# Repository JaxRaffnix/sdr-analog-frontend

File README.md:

# SDR Analog Frontend

The PCB is ordered from [Aisler](https://aisler.net/p/YPFMCLNO).

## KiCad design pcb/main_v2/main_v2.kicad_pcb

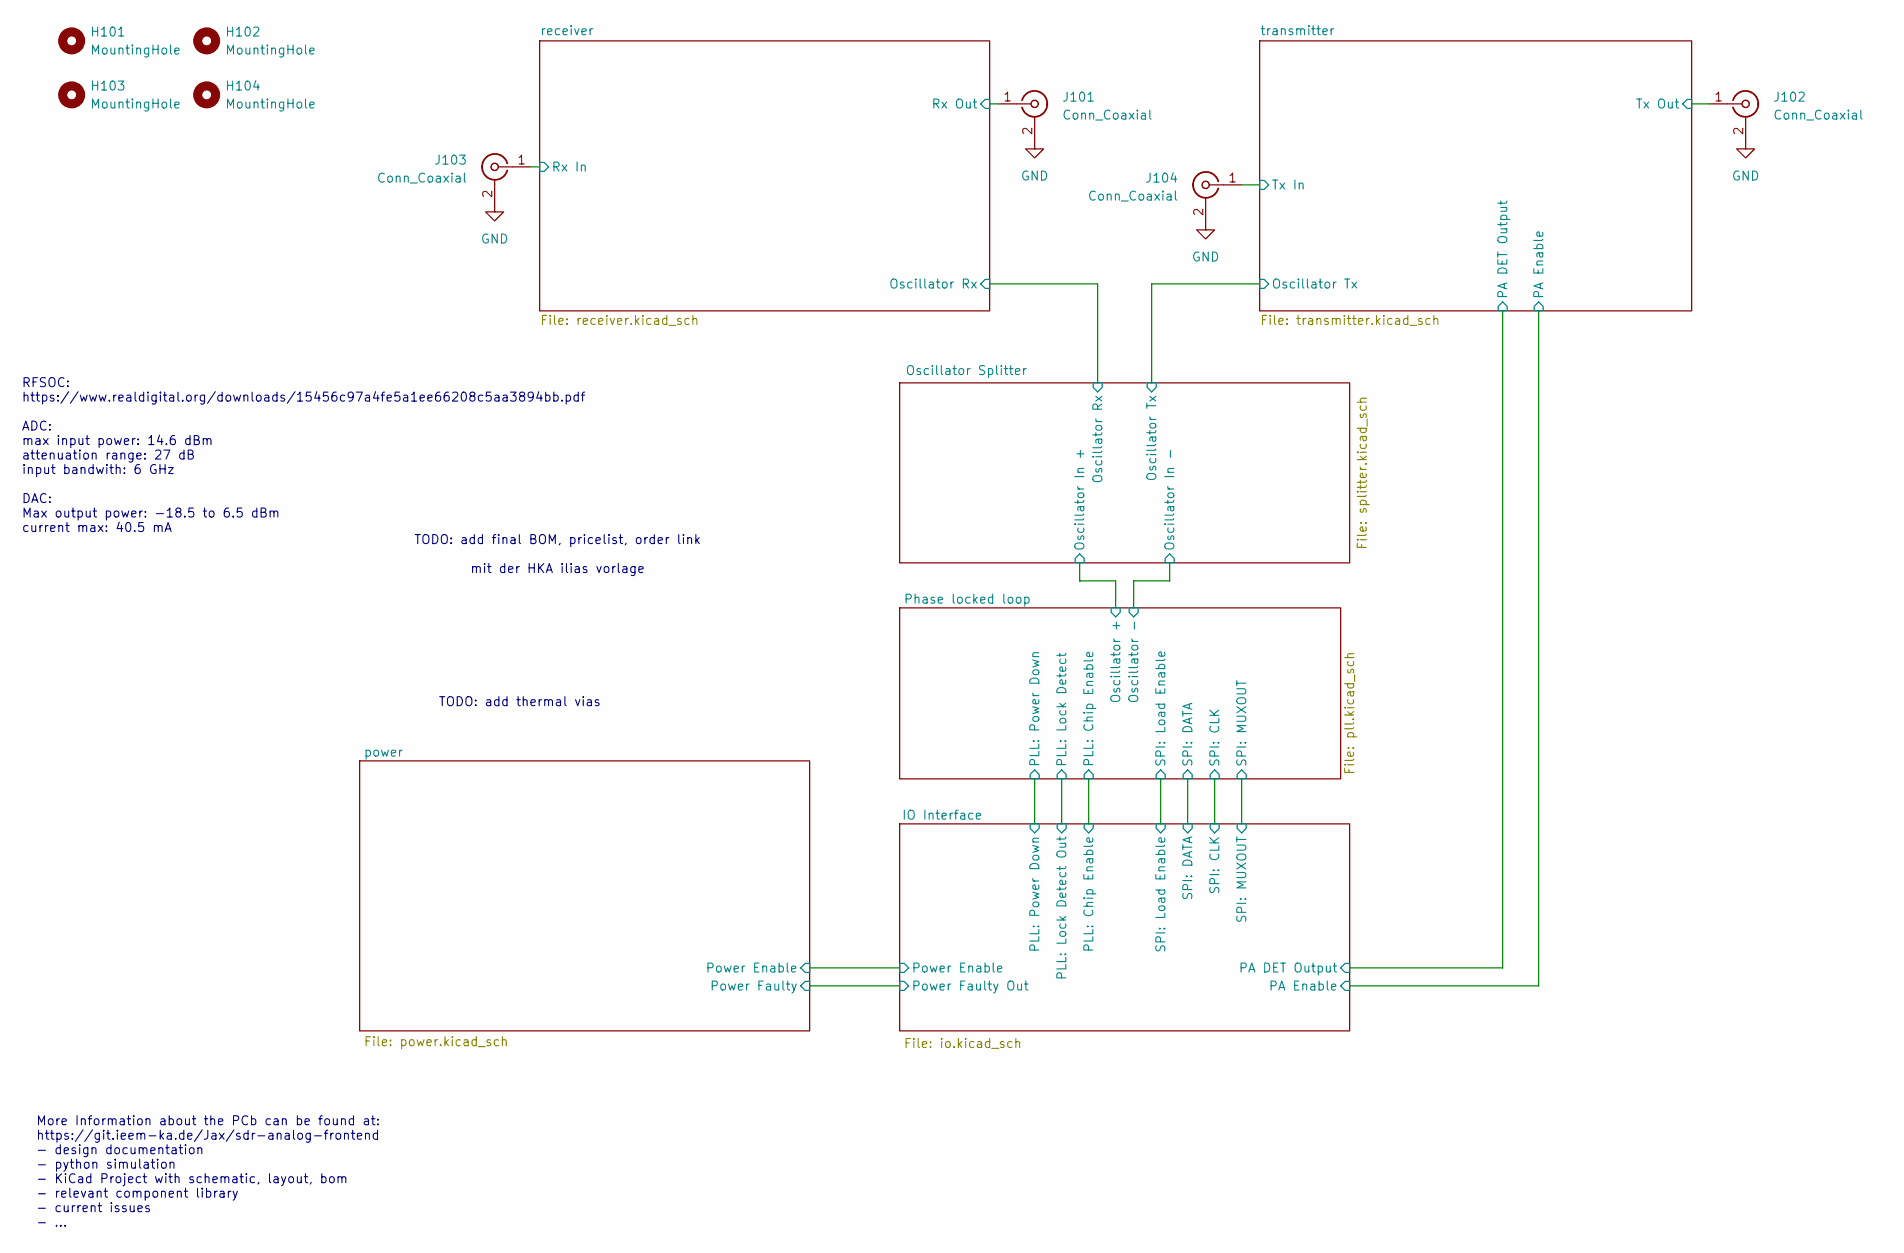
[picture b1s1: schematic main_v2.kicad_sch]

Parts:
H101, H102, H103, H104: MountingHole; MountingHole_2.2mm_M2
J101, J102, J103, J104: Conn_Coaxial; SMA_Amphenol_132289_EdgeMount

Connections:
/receiver/Rx In: J103.1 (In); also elsewhere on the board
/receiver/Rx Out: J101.1 (In); also elsewhere on the board
/transmitter/Tx In: J104.1 (In); also elsewhere on the board
/transmitter/Tx Out: J102.1 (In); also elsewhere on the board
GND: J101.2 (Ext), J102.2 (Ext), J103.2 (Ext), J104.2 (Ext); also elsewhere on the board

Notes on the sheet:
TODO: add final BOM, pricelist, order link mit der HKA ilias vorlage
TODO: add thermal vias
More Information about the PCb can be found at: https://git.ieem-ka.de/Jax/sdr-analog-frontend - design documentation - python simulation - KiCad Project with schematic, layout, bom - relevant component library - current issues - ...
RFSOC: https://www.realdigital.org/downloads/15456c97a4fe5a1ee66208c5aa3894bb.pdf ADC: max input power: 14.6 dBm attenuation range: 27 dB input bandwith: 6 GHz DAC: Max output power: -18.5 to 6.5 dBm current max: 40.5 mA

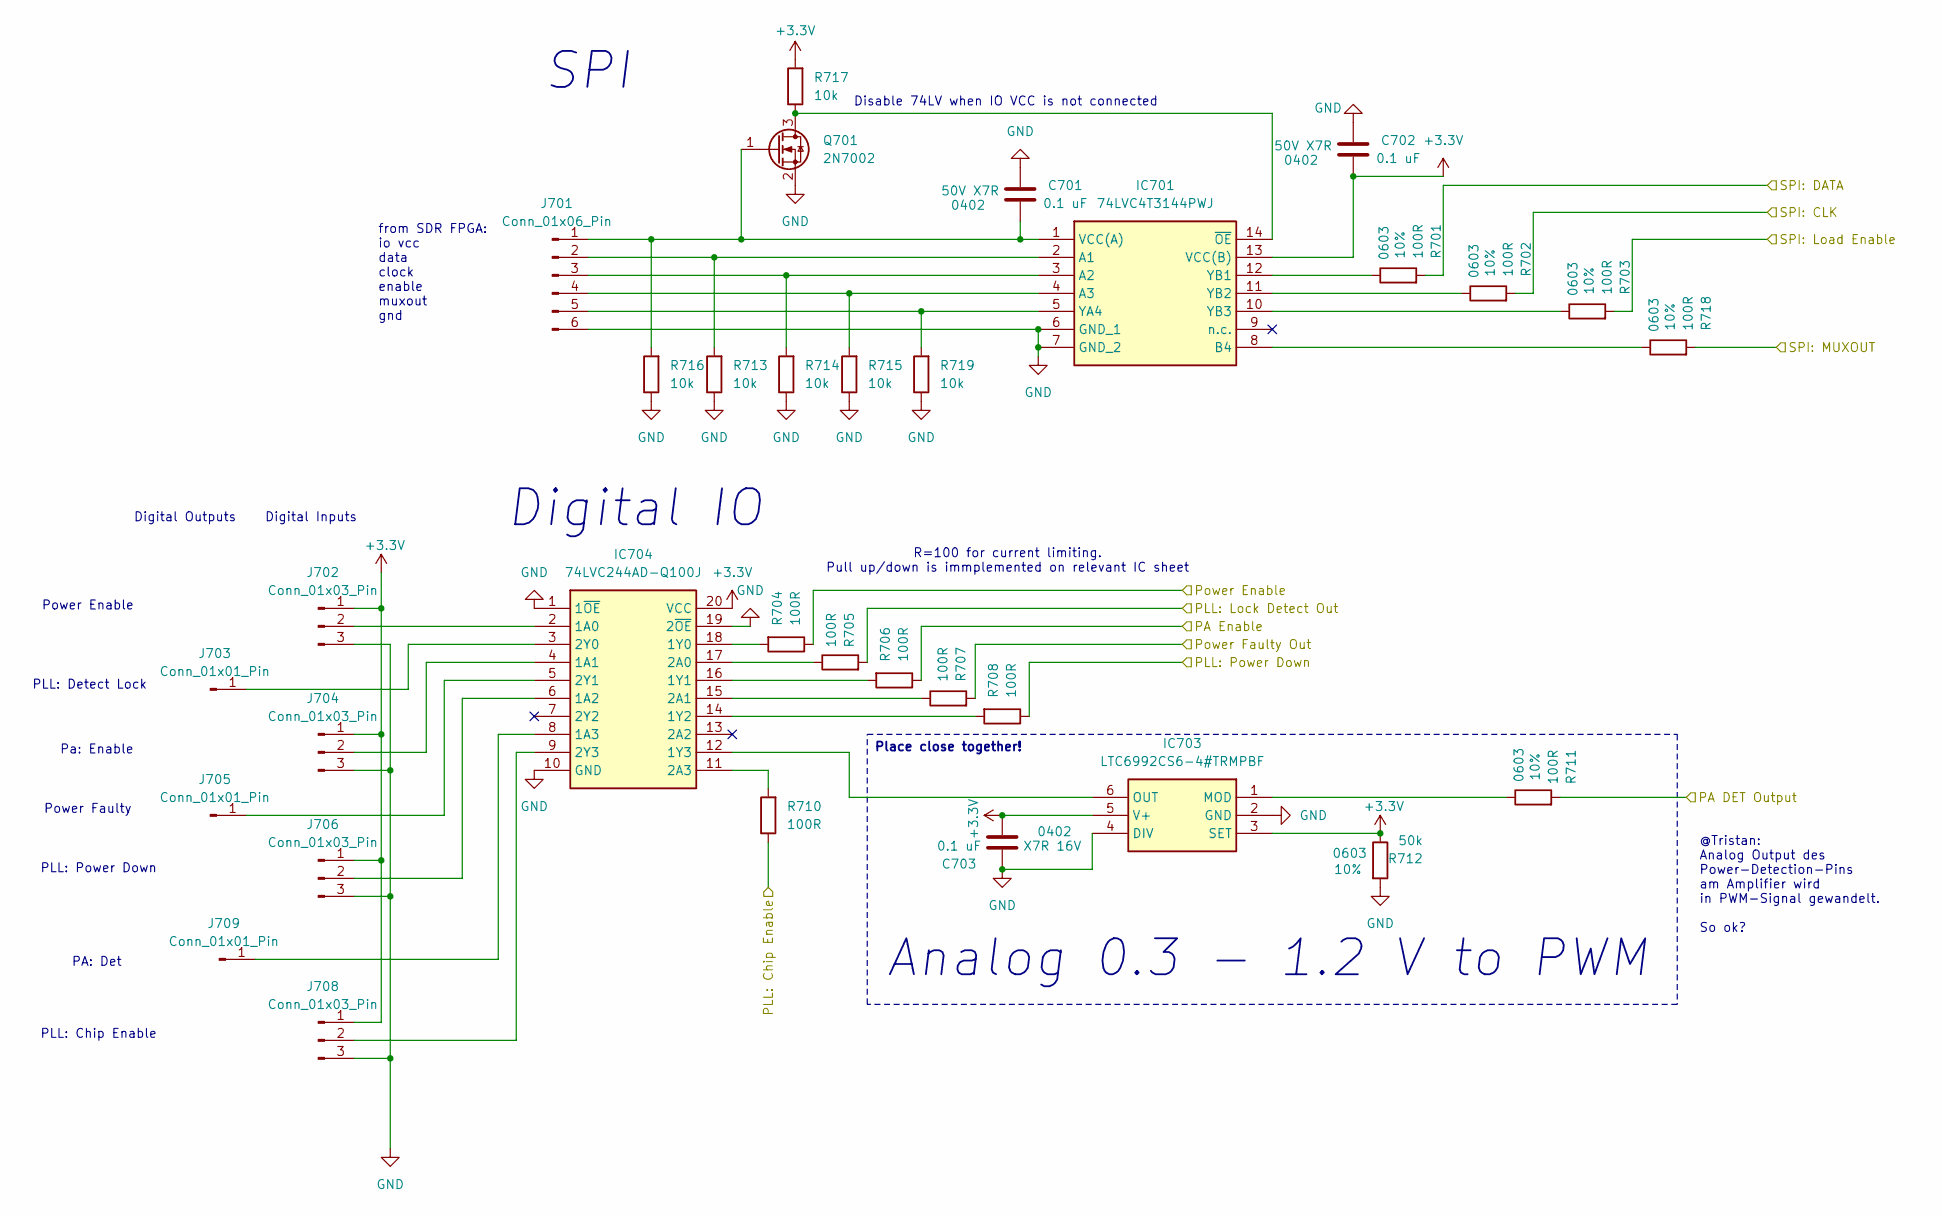
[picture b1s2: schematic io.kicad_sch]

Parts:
C701, C702: 0.1 uF; C_0402_1005Metric; Tolerance ±10%; Voltage 50V
C703: 0.1 uF; C_0402_1005Metric; Tolerance ±10%; Voltage 16V
IC701: 74LVC4T3144PWJ; SOP65P640X110-14N; Mouser Part Number 771-74LVC4T3144PWJ
IC703: LTC6992CS6-4#TRMPBF; SOT95P280X100-6N; Mouser Part Number 584-C6992CS6-4TRMPBF
IC704: 74LVC244AD-Q100J; SOIC127P1032X265-20N; Mouser Part Number 771-74LVC244AD-Q100J
J701: Conn_01x06_Pin; PinHeader_1x06_P2.54mm_Vertical
J702, J704, J706, J708: Conn_01x03_Pin; PinHeader_1x03_P2.54mm_Vertical
J703, J705, J709: Conn_01x01_Pin; PinHeader_1x01_P2.54mm_Vertical
Q701: 2N7002; SOT-23
R701, R702, R703, R711, R718: 100R; R_0603_1608Metric; Tolerance 10%
R704, R705, R706, R707, R708, R710: 100R; R_0603_1608Metric
R712: 50k; R_0603_1608Metric; Tolerance 10%
R713, R714, R715, R716, R717, R719: 10k; R_0603_1608Metric

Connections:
+3.3V: C702.1, C703.1, IC701.13 (VCC(B)), IC703.3 (SET), IC703.5 (V+), IC704.20 (VCC), J702.1, J704.1, J706.1, J708.1, R712.1, R717.2; also elsewhere on the board
/IO Interface/PA DET Output: R711.2; also elsewhere on the board
/IO Interface/PA Enable: R706.1; also elsewhere on the board
/IO Interface/PLL: Chip Enable: R710.1; also elsewhere on the board
/IO Interface/PLL: Lock Detect Out: R705.2; also elsewhere on the board
/IO Interface/PLL: Power Down: R708.1; also elsewhere on the board
/IO Interface/Power Enable: R704.1; also elsewhere on the board
/IO Interface/Power Faulty Out: R707.2; also elsewhere on the board
/IO Interface/SPI: CLK: R702.2; also elsewhere on the board
/IO Interface/SPI: DATA: R701.2; also elsewhere on the board
/IO Interface/SPI: Load Enable: R703.2; also elsewhere on the board
/IO Interface/SPI: MUXOUT: R718.2; also elsewhere on the board
GND: C701.2, C702.2, C703.2, IC701.6 (GND_1), IC701.7 (GND_2), IC703.2 (GND), IC703.4 (DIV), IC704.1 (1~OE), IC704.10 (GND), IC704.19 (2~OE), J701.6, J702.3, J704.3, J706.3, J708.3, Q701.2 (S), R712.2, R713.1, R714.1, R715.1, R716.1, R719.1; also elsewhere on the board
unnamed: IC701.2 (A1), J701.2, R713.2
unnamed: IC701.3 (A2), J701.3, R714.2
unnamed: IC701.4 (A3), J701.4, R715.2
unnamed: IC701.8 (B4), R718.1
unnamed: C701.1, IC701.1 (VCC(A)), J701.1, Q701.1 (G), R716.2
unnamed: IC701.5 (YA4), J701.5, R719.2
unnamed: IC701.12 (YB1), R701.1
unnamed: IC701.11 (YB2), R702.1
unnamed: IC701.10 (YB3), R703.1
unnamed: IC701.14 (~OE), Q701.3 (D), R717.1
unnamed: IC703.1 (MOD), R711.1
unnamed: IC703.6 (OUT), IC704.12 (1Y3)
unnamed: IC704.2 (1A0), J702.2
unnamed: IC704.4 (1A1), J704.2
unnamed: IC704.6 (1A2), J706.2
unnamed: IC704.8 (1A3), J709.1 (Pin_1_1)
unnamed: IC704.18 (1Y0), R704.2
unnamed: IC704.16 (1Y1), R706.2
unnamed: IC704.14 (1Y2), R708.2
unnamed: IC704.17 (2A0), R705.1
unnamed: IC704.15 (2A1), R707.1
unnamed: IC704.11 (2A3), R710.2
unnamed: IC704.3 (2Y0), J703.1 (Pin_1_1)
unnamed: IC704.5 (2Y1), J705.1 (Pin_1_1)
unnamed: IC704.9 (2Y3), J708.2

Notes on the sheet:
Power Enable
Analog 0.3 - 1.2 V to PWM
R=100 for current limiting. Pull up/down is immplemented on relevant IC sheet
PLL: Power Down
Digital IO
from SDR FPGA: io vcc data clock enable muxout gnd
Digital Inputs
PA: Det
Disable 74LV when IO VCC is not connected
Power Faulty
Digital Outputs
@Tristan: Analog Output des Power-Detection-Pins am Amplifier wird in PWM-Signal gewandelt. So ok?
PLL: Chip Enable
Pa: Enable
PLL: Detect Lock
SPI
Place close together!

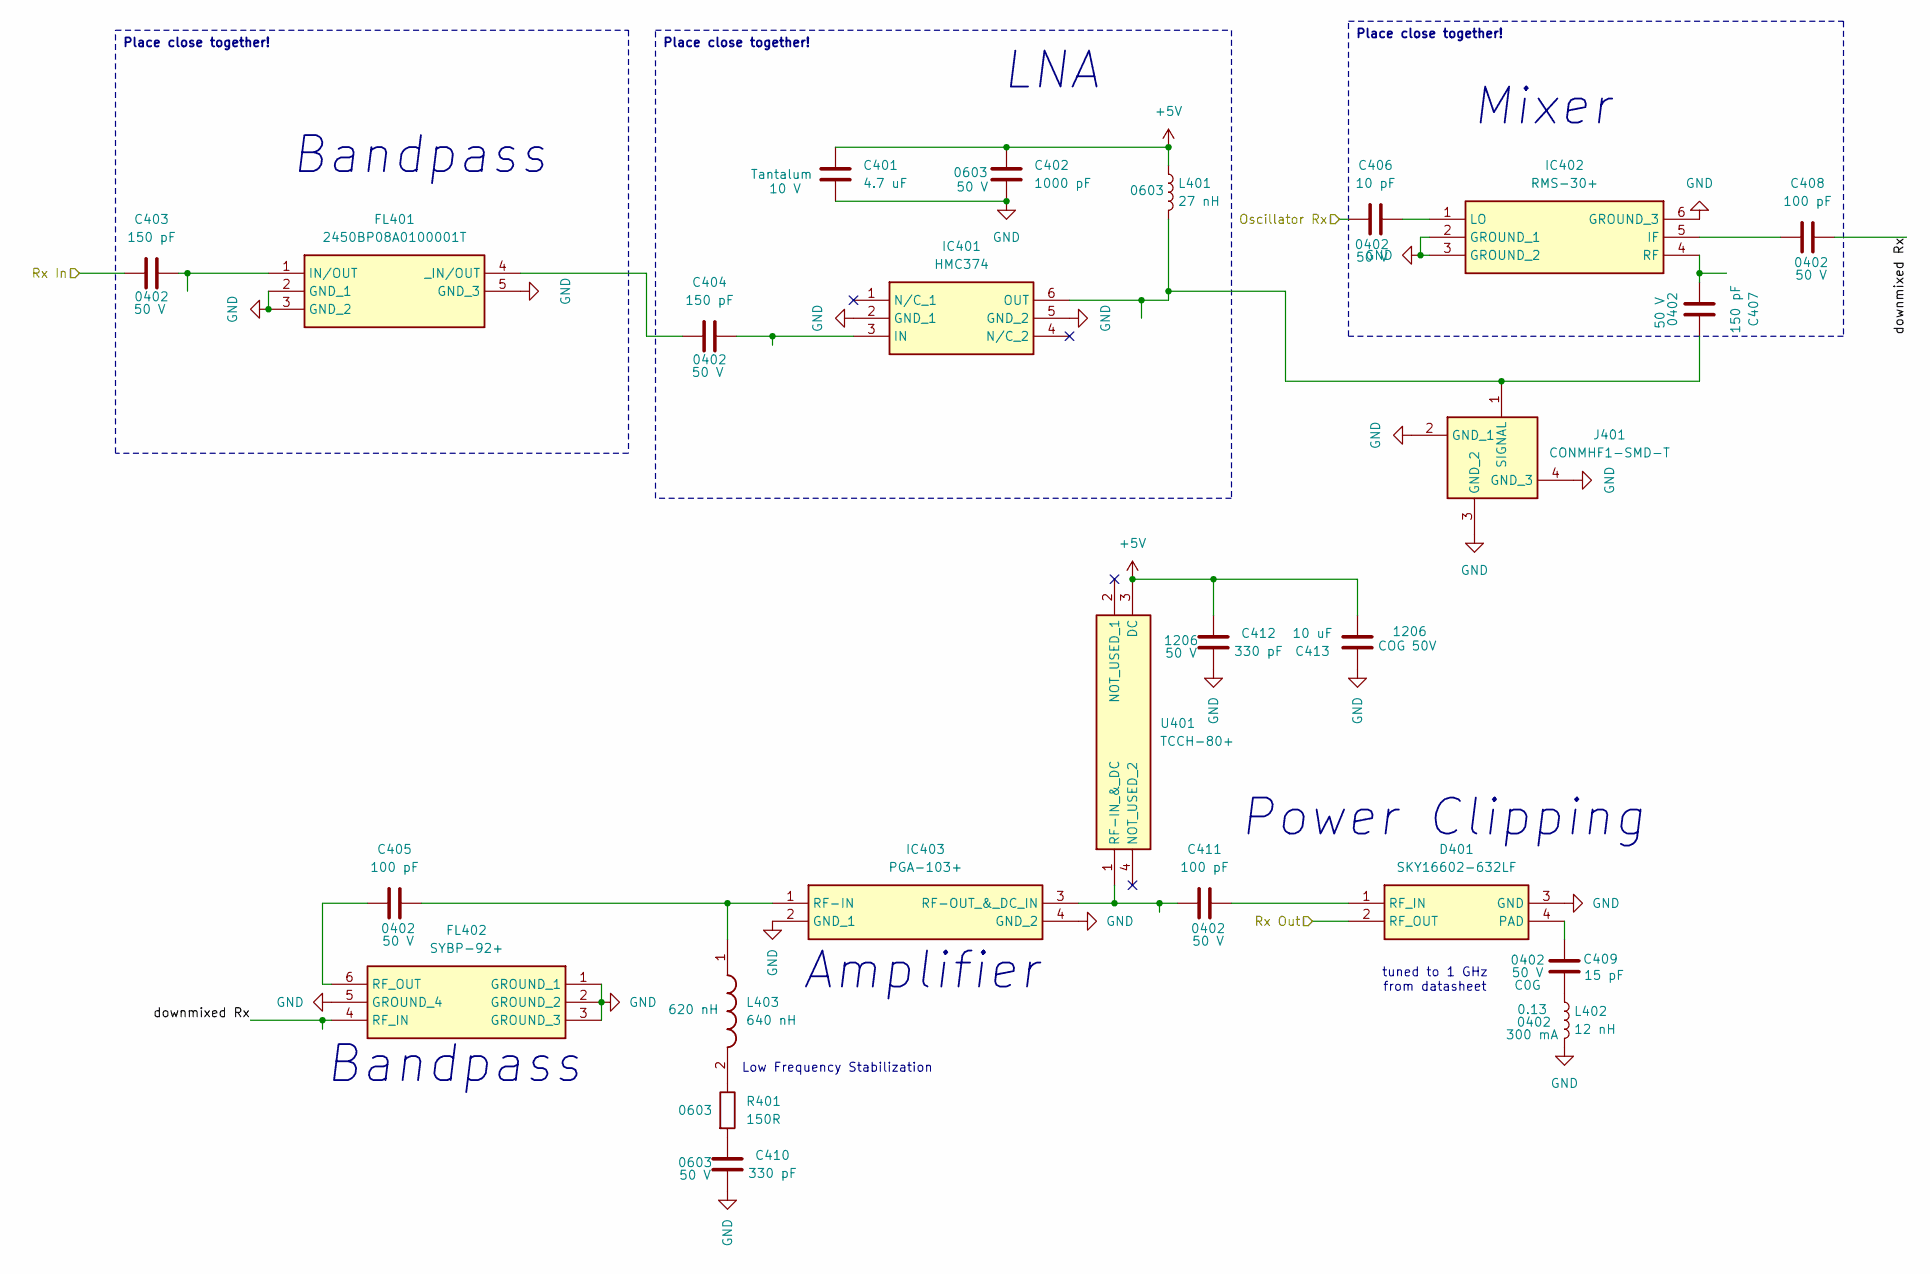
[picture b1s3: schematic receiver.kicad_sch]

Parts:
C401: 4.7 uF; CP_EIA-6032-20_AVX-F; Voltage 10 V
C402: 1000 pF; C_0603_1608Metric; Voltage 50 V
C403, C404, C407: 150 pF; C_0402_1005Metric; Voltage 50 V
C405, C408, C411: 100 pF; C_0402_1005Metric; Voltage 50 V
C406: 10 pF; C_0402_1005Metric; Voltage 50 V
C409: 15 pF; C_0402_1005Metric; Voltage 50 V
C410: 330 pF; C_0603_1608Metric; Voltage 50 V
C412: 330 pF; C_1206_3216Metric; Voltage 50 V
C413: 10 uF; C_1206_3216Metric; Tolerance ±10%; Voltage 50V
D401: SKY16602-632LF; SKY16602632LF; Mouser Part Number 873-SKY16602-632LF
FL401: 2450BP08A0100001T; Manufacturer_Part_Number 2450BP08A0100001T
FL402: SYBP-92+; SYBP92; Mouser Part Number 139-SYBP-92+
IC401: HMC374; SOT95P280X145-6N; Mouser Part Number 584-HMC374
IC402: RMS-30+; RMS30; Manufacturer_Part_Number RMS-30+
IC403: PGA-103+; GVA63; Mouser Part Number 139-PGA-103
J401: CONMHF1-SMD-T; CONMHF1SMDT; Mouser Part Number 712-CONMHF1-SMD-T
L401: 27 nH; L_0603_1608Metric
L402: 12 nH; L_0402_1005Metric
L403: 640 nH; L_0402_1005Metric
R401: 150R; R_0603_1608Metric; Tolerance 5%
U401: TCCH-80+; TCCH80; Mouser Part Number 139-TCCH-80

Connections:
+5V: C401.1, C402.2, C412.1, C413.1, L401.1, U401.3 (DC); also elsewhere on the board
/Oscillator Splitter/Oscillator Rx: C406.2; also elsewhere on the board
/receiver/Rx In: C403.1; also elsewhere on the board
/receiver/Rx Out: D401.2 (RF_OUT); also elsewhere on the board
/receiver/downmixed Rx: C408.2, FL402.4 (RF_IN)
GND: C401.2, C402.1, C410.2, C412.2, C413.2, D401.3 (GND), FL401.2 (GND_1), FL401.3 (GND_2), FL401.5 (GND_3), FL402.1 (GROUND_1), FL402.2 (GROUND_2), FL402.3 (GROUND_3), FL402.5 (GROUND_4), IC401.2 (GND_1), IC401.5 (GND_2), IC402.2 (GROUND_1), IC402.3 (GROUND_2), IC402.6 (GROUND_3), IC403.2 (GND_1), IC403.4 (GND_2), J401.2 (GND_1), J401.3 (GND_2), J401.4 (GND_3), L402.2; also elsewhere on the board
unnamed: C409.2, L402.1
unnamed: C410.1, R401.2
unnamed: C409.1, D401.4 (PAD)
unnamed: C411.2, D401.1 (RF_IN)
unnamed: C403.2, FL401.1 (IN/OUT)
unnamed: C404.1, FL401.4 (_IN/OUT)
unnamed: C405.1, FL402.6 (RF_OUT)
unnamed: C404.2, IC401.3 (IN)
unnamed: C407.2, IC401.6 (OUT), J401.1 (SIGNAL), L401.2
unnamed: C408.1, IC402.5 (IF)
unnamed: C406.1, IC402.1 (LO)
unnamed: C407.1, IC402.4 (RF)
unnamed: C405.2, IC403.1 (RF-IN), L403.1
unnamed: C411.1, IC403.3 (RF-OUT_&_DC_IN), U401.1 (RF-IN_&_DC)
unnamed: L403.2, R401.1

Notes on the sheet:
Low Frequency Stabilization
Bandpass
Amplifier
LNA
Power Clipping
tuned to 1 GHz from datasheet
Mixer
Place close together!

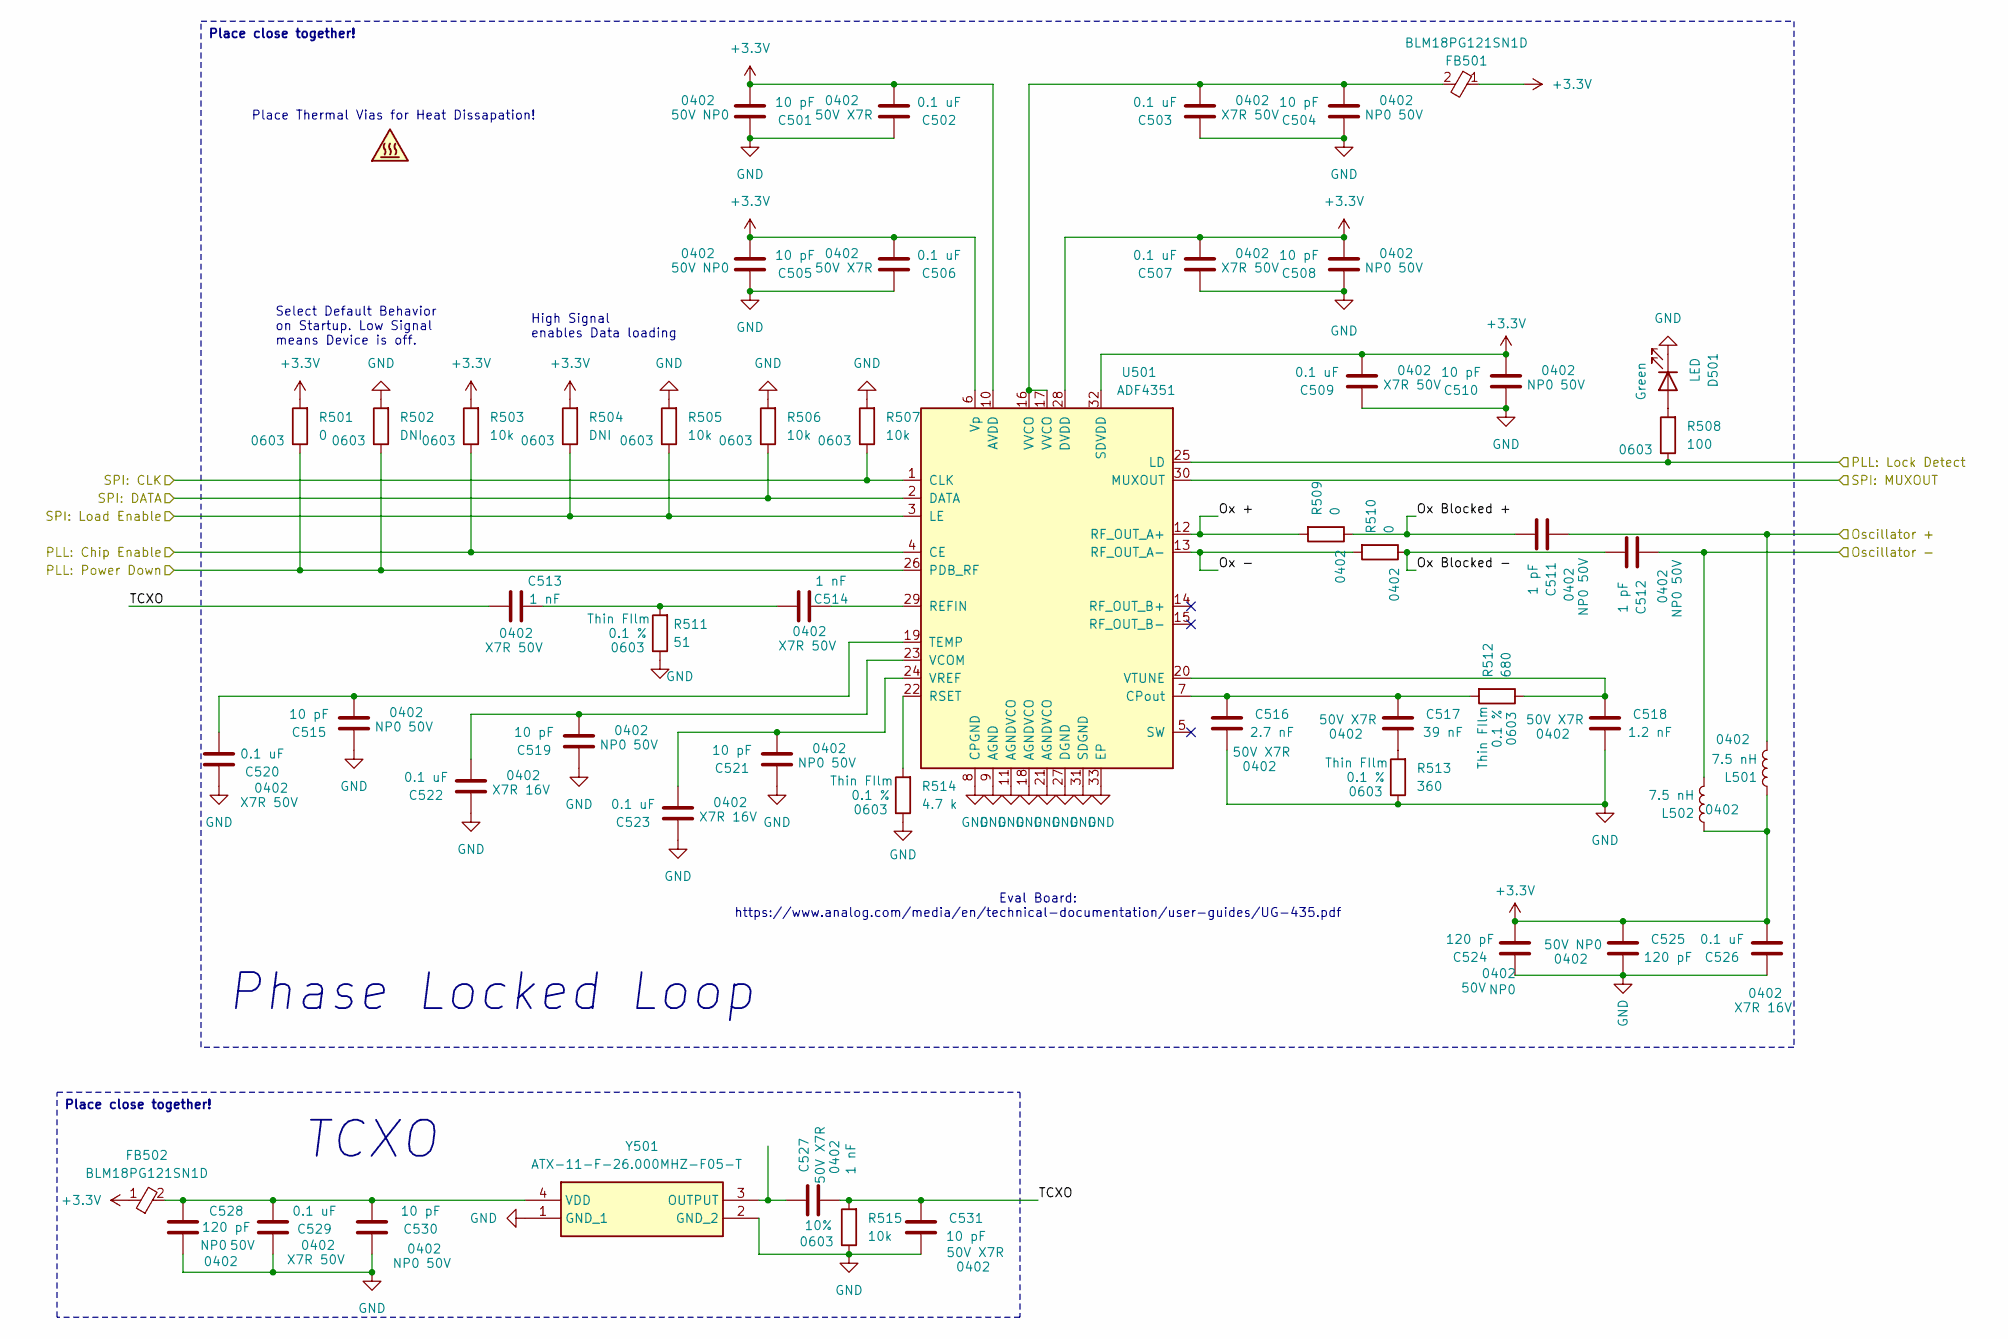
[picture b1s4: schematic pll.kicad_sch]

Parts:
C501, C504, C505, C508, C510, C515, C519, C521, C530, C531: 10 pF; C_0402_1005Metric; Tolerance ±10%; Voltage 50V
C502, C503, C506, C507, C509, C520, C529: 0.1 uF; C_0402_1005Metric; Tolerance ±10%; Voltage 50V
C511, C512: 1 pF; C_0402_1005Metric; Tolerance ±10%; Voltage 50V
C513, C514, C527: 1 nF; C_0402_1005Metric; Tolerance ±10%; Voltage 50V
C516: 2.7 nF; C_0402_1005Metric; Tolerance ±10%; Voltage 50V
C517: 39 nF; C_0402_1005Metric; Tolerance ±10%; Voltage 50V
C518: 1.2 nF; C_0402_1005Metric; Tolerance ±10%; Voltage 50V
C522, C523, C526: 0.1 uF; C_0402_1005Metric; Tolerance ±10%; Voltage 16V
C524, C525, C528: 120 pF; C_0402_1005Metric; Tolerance ±10%; Voltage 50V
D501: LED; LED_0805_2012Metric
FB501, FB502: BLM18PG121SN1D; BLM18SP221SN1B; Mouser Part Number 81-BLM18PG121SN1D
L501, L502: 7.5 nH; L_0402_1005Metric
R501, R509, R510: 0; R_0603_1608Metric
R502, R504: DNI; R_0603_1608Metric
R503, R505, R506, R507: 10k; R_0603_1608Metric
R508: 100; R_0603_1608Metric
R511: 51; R_0603_1608Metric; Tolerance 0.1 %
R512: 680; R_0603_1608Metric; Tolerance 0.1 %
R513: 360; R_0603_1608Metric; Tolerance 0.1 %
R514: 4.7 k; R_0603_1608Metric; Tolerance 0.1 %
R515: 10k; R_0603_1608Metric; Tolerance 10%
U501: ADF4351; LFCSP-32-1EP_5x5mm_P0.5mm_EP3.25x3.25mm
Y501: ATX-11-F-26.000MHZ-F05-T; ATX11F26000MHZF05T; Manufacturer_Part_Number ATX-11-F-26.000MHZ-F05-T

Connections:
+3.3V: C501.1, C502.1, C505.1, C506.1, C507.1, C508.1, C509.1, C510.1, C524.1, C525.2, C526.1, FB501.1, FB502.1, L501.1, L502.1, R501.2, R503.2, R504.2, U501.6 (Vp), U501.10 (AVDD), U501.28 (DVDD), U501.32 (SDVDD); also elsewhere on the board
/IO Interface/PLL: Chip Enable: R503.1, U501.4 (CE); also elsewhere on the board
/IO Interface/PLL: Lock Detect Out: R508.1, U501.25 (LD); also elsewhere on the board
/IO Interface/PLL: Power Down: R501.1, R502.1, U501.26 (PDB_RF); also elsewhere on the board
/IO Interface/SPI: CLK: R507.1, U501.1 (CLK); also elsewhere on the board
/IO Interface/SPI: DATA: R506.1, U501.2 (DATA); also elsewhere on the board
/IO Interface/SPI: Load Enable: R504.1, R505.1, U501.3 (LE); also elsewhere on the board
/IO Interface/SPI: MUXOUT: U501.30 (MUXOUT); also elsewhere on the board
/Oscillator Splitter/Oscillator In +: C511.2, L501.2; also elsewhere on the board
/Oscillator Splitter/Oscillator In -: C512.2, L502.2; also elsewhere on the board
/Phase locked loop/Ox +: R509.2, U501.12 (RF_OUT_A+)
/Phase locked loop/Ox -: R510.2, U501.13 (RF_OUT_A-)
/Phase locked loop/Ox Blocked +: C511.1, R509.1
/Phase locked loop/Ox Blocked -: C512.1, R510.1
/Phase locked loop/TCXO: C513.2, C527.1, C531.2, R515.2
GND: C501.2, C502.2, C503.2, C504.2, C505.2, C506.2, C507.2, C508.2, C509.2, C510.2, C515.2, C516.1, C518.1, C519.2, C520.2, C521.2, C522.2, C523.2, C524.2, C525.1, C526.2, C528.1, C529.2, C530.2, C531.1, D501.1 (K), R502.2, R505.2, R506.2, R507.2, R511.1, R513.1, R514.1, R515.1, U501.8 (CPGND), U501.9 (AGND), U501.11 (AGNDVCO), U501.18 (AGNDVCO), U501.21 (AGNDVCO), U501.27 (DGND), U501.31 (SDGND), U501.33 (EP), Y501.1 (GND_1), Y501.2 (GND_2); also elsewhere on the board
unnamed: C503.1, C504.1, FB501.2, U501.16 (VVCO), U501.17 (VVCO)
unnamed: C513.1, C514.2, R511.2
unnamed: C517.1, R513.2
unnamed: D501.2 (A), R508.2
unnamed: C516.2, C517.2, R512.2, U501.7 (CPout)
unnamed: C514.1, U501.29 (REFIN)
unnamed: R514.2, U501.22 (RSET)
unnamed: C515.1, C520.1, U501.19 (TEMP)
unnamed: C519.1, C522.1, U501.23 (VCOM)
unnamed: C521.1, C523.1, U501.24 (VREF)
unnamed: C518.2, R512.1, U501.20 (VTUNE)
unnamed: C527.2, Y501.3 (OUTPUT)
unnamed: C528.2, C529.1, C530.1, FB502.2, Y501.4 (VDD)

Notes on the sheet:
TCXO
Eval Board: https://www.analog.com/media/en/technical-documentation/user-guides/UG-435.pdf
Select Default Behavior on Startup. Low Signal means Device is off.
Place Thermal Vias for Heat Dissapation!
High Signal enables Data loading
Phase Locked Loop
Place close together!

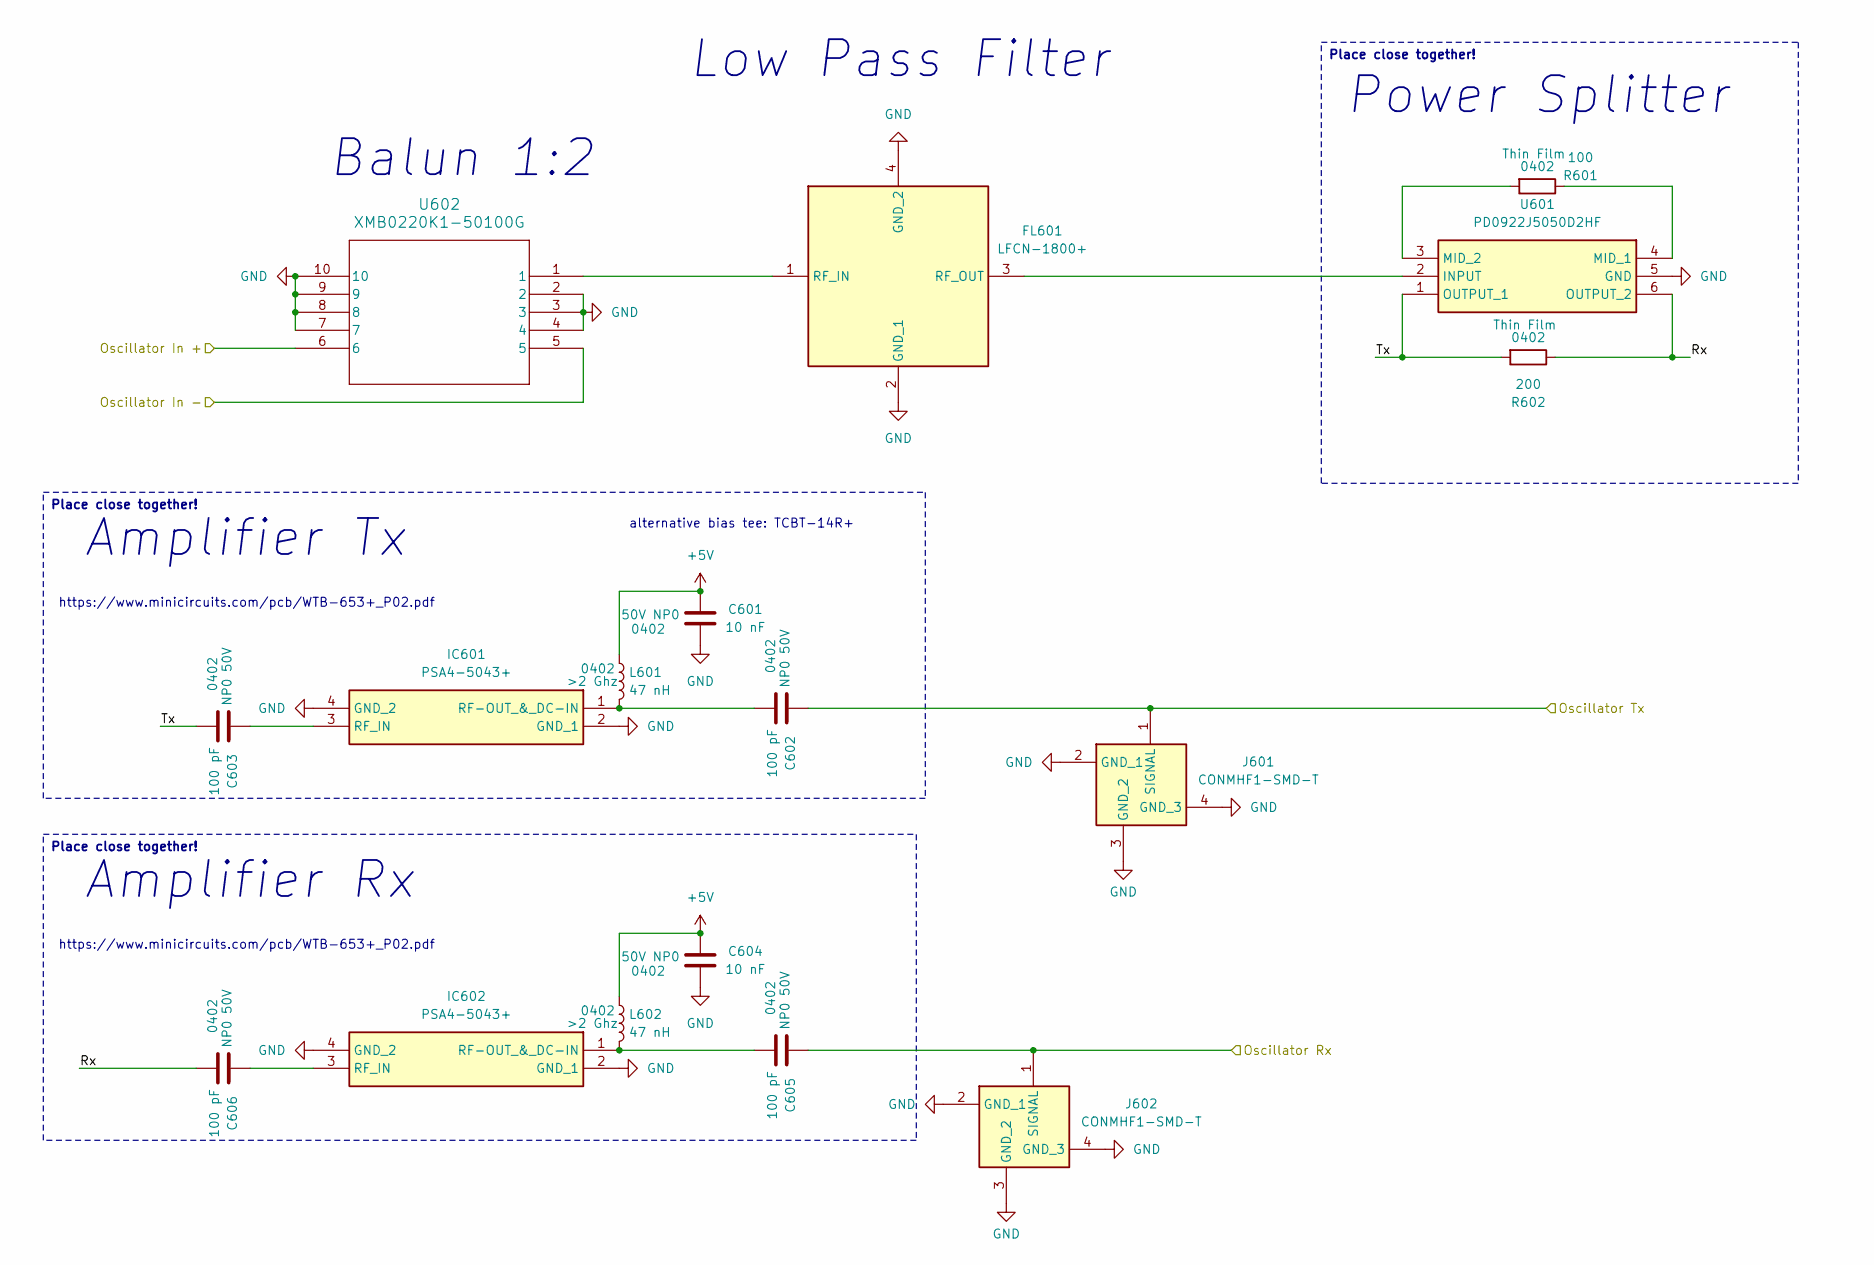
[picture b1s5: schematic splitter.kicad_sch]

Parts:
C601, C604: 10 nF; C_0402_1005Metric; Tolerance ±10%; Voltage 50V
C602, C603, C605, C606: 100 pF; C_0402_1005Metric; Tolerance ±10%; Voltage 50V
FL601: LFCN-1800+; LFCN1800; Mouser Part Number 139-LFCN-1800
IC601, IC602: PSA4-5043+; PSA45043; Mouser Part Number 139-PSA4-5043
J601, J602: CONMHF1-SMD-T; CONMHF1SMDT; Mouser Part Number 712-CONMHF1-SMD-T
L601, L602: 47 nH; L_0402_1005Metric
R601: 100; R_0402_1005Metric
R602: 200; R_0402_1005Metric
U601: PD0922J5050D2HF; Mouser Part Number 620-PD0922J5050D2HF
U602: XMB0220K1-50100G; XMB0220K1-50100G_TTT

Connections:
+5V: C601.2, C604.2, L601.1, L602.1; also elsewhere on the board
/Oscillator Splitter/Oscillator In +: U602.6; also elsewhere on the board
/Oscillator Splitter/Oscillator In -: U602.5; also elsewhere on the board
/Oscillator Splitter/Oscillator Rx: C605.2, J602.1 (SIGNAL); also elsewhere on the board
/Oscillator Splitter/Oscillator Tx: C602.2, J601.1 (SIGNAL); also elsewhere on the board
/Oscillator Splitter/Rx: C606.1, R602.1, U601.6 (OUTPUT_2)
/Oscillator Splitter/Tx: C603.1, R602.2, U601.1 (OUTPUT_1)
GND: C601.1, C604.1, FL601.2 (GND_1), FL601.4 (GND_2), IC601.2 (GND_1), IC601.4 (GND_2), IC602.2 (GND_1), IC602.4 (GND_2), J601.2 (GND_1), J601.3 (GND_2), J601.4 (GND_3), J602.2 (GND_1), J602.3 (GND_2), J602.4 (GND_3), U601.5 (GND), U602.2, U602.3, U602.4, U602.7, U602.8, U602.9, U602.10; also elsewhere on the board
unnamed: FL601.1 (RF_IN), U602.1
unnamed: FL601.3 (RF_OUT), U601.2 (INPUT)
unnamed: C602.1, IC601.1 (RF-OUT_&_DC-IN), L601.2
unnamed: C603.2, IC601.3 (RF_IN)
unnamed: C605.1, IC602.1 (RF-OUT_&_DC-IN), L602.2
unnamed: C606.2, IC602.3 (RF_IN)
unnamed: R601.1, U601.4 (MID_1)
unnamed: R601.2, U601.3 (MID_2)

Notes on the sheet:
Low Pass Filter
Power Splitter
https://www.minicircuits.com/pcb/WTB-653+_P02.pdf
Balun 1:2
Amplifier Rx
alternative bias tee: TCBT-14R+
Amplifier Tx
Place close together!
